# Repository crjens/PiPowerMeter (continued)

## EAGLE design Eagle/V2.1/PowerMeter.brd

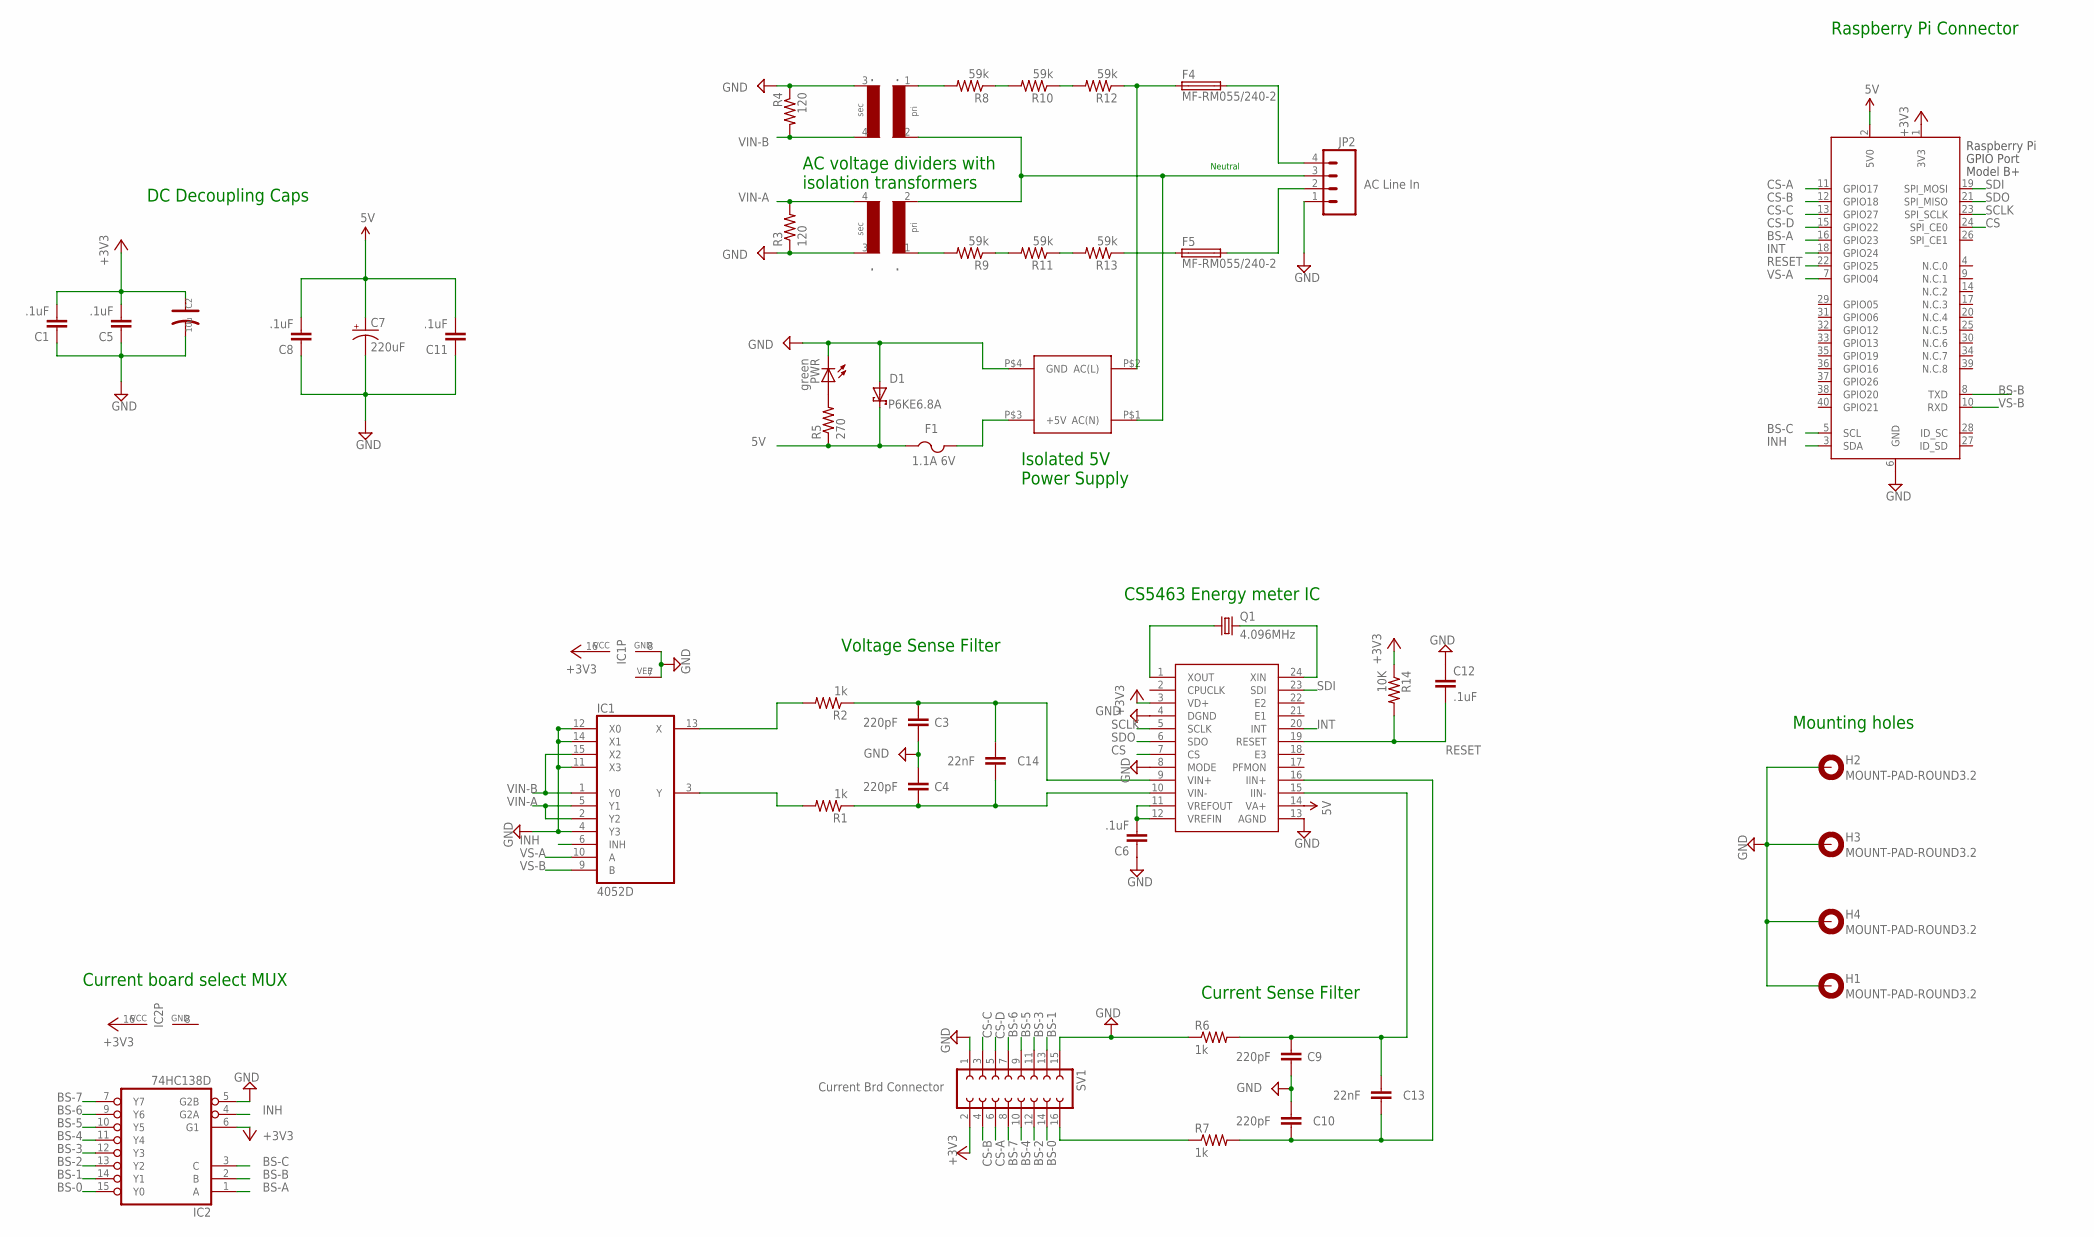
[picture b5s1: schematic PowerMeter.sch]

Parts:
C1, C5, C6, C8, C11, C12: .1uF; C1206; PARTNO C1206C104K5RAC7867
C2: 10u; AVX-C; PARTNO T491C106K016AT
C3, C4, C9, C10: 220pF; C1206; PARTNO C1206C221J5GACTU
C7: 220uF; E2,5-6E; PARTNO ESH227M016AE3AA
C13, C14: 22nF; C1206; PARTNO C1206C223K5RACTU
D1: P6KE6.8A; C1702-15; PARTNO P6KE6.8A
F1: 1.1A 6V; 1812; PARTNO 0ZCC0110AF2C
F4, F5: MF-RM055/240-2; TE5; PARTNO MF-RM055/240-2
H1, H2, H3, H4: MOUNT-PAD-ROUND3.2; 3,2-PAD
IC1: 4052D; SO16; PARTNO CD4052BNSR
IC2: 74HC138D; SO16; PARTNO SN74HC138NSR
JP2: AC Line In; SCREWTERMINAL-5MM-4; PARTNO 1935187
PWR: green; LED_1206; PARTNO LTST-C150GKT
Q1: 4.096MHz; HC49/S; PARTNO 9B-4.096MBBK-B
R1, R2, R6, R7: 1k; R1206; PARTNO RC1206FR-071KL
R3, R4: 120; R1206; PARTNO RC1206FR-07120RL
R5: 270; R1206; PARTNO RC1206FR-07270RL
R8, R9, R10, R11, R12, R13: 59k; R1206; PARTNO RC1206FR-0759KL
R14: 10K; R1206; PARTNO RC1206FR-0710KL
SV1: Current Brd Connector; FE08-2; PARTNO PPTC082LFBN-RC
U$2, U$3: TV16E
U$4: VSK-S10; PARTNO VSK-S5-5UA
U$5: CS5463; SSOP24; PARTNO CS5463-ISZ
X2: RASPI_BOARD_B+_E4; RASPI_BOARD_B+_EDGES_4DRILL; PARTNO M20-9762046

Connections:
5V: C7.+, C8.2, C11.2, D1.C, F1.1, R5.1, U$5.14 (VA+), X2.2 (5V0)
+3V3: C1.2, C2.+, C5.2, IC1.16 (VCC), IC2.6 (G1), IC2.16 (VCC), R14.1, SV1.2, U$5.3 (VD+), X2.1 (3V3)
+5V: F1.2, U$4.P$3 (+5V)
AC1: R8.2, U$3.1
AC(L): F4.1, R12.1, U$4.P$2 (AC(L))
AC(N): JP2.3, U$2.2, U$3.2, U$4.P$1 (AC(N))
BS-0: IC2.15 (Y0), SV1.14
BS-1: IC2.14 (Y1), SV1.13
BS-2: IC2.13 (Y2), SV1.12
BS-3: IC2.12 (Y3), SV1.11
BS-4: IC2.11 (Y4), SV1.10
BS-5: IC2.10 (Y5), SV1.9
BS-6: IC2.9 (Y6), SV1.7
BS-7: IC2.7 (Y7), SV1.8
BS-A: IC2.1 (A), X2.16 (GPIO23)
BS-B: IC2.2 (B), X2.8 (TXD)
BS-C: IC2.3 (C), X2.5 (SCL)
C5: C10.1, C13.1, R7.2, U$5.16 (IIN+)
CS: U$5.7 (CS), X2.24 (SPI_CE0)
CS-A: SV1.6, X2.11 (GPIO17)
CS-B: SV1.4, X2.12 (GPIO18)
CS-C: SV1.3, X2.13 (GPIO27)
CS-D: SV1.5, X2.15 (GPIO22)
GND: C1.1, C2.-, C3.1, C4.2, C5.1, C6.1, C7.-, C8.1, C9.1, C10.2, C11.1, C12.1, D1.A, H1.B3,2, H2.B3,2, H3.B3,2, H4.B3,2, IC1.4 (Y3), IC1.7 (VEE), IC1.8 (GND), IC1.11 (X3), IC1.12 (X0), IC1.14 (X1), IC2.5 (G2B), IC2.8 (GND), JP2.1, PWR.C, R3.1, R4.1, R6.1, SV1.1, SV1.15, U$2.3, U$3.3, U$4.P$4 (GND), U$5.4 (DGND), U$5.8 (MODE), U$5.13 (AGND), X2.6 (GND)
IIN+: R7.1, SV1.16
INH: IC1.6 (INH), IC2.4 (G2A), X2.3 (SDA)
INT: U$5.20 (INT), X2.18 (GPIO24)
unnamed: Q1.1, U$5.1 (XOUT)
unnamed: F5.1, R13.1
unnamed: PWR.A, R5.2
unnamed: C9.2, C13.2, R6.2, U$5.15 (IIN-)
unnamed: F4.2, JP2.4
unnamed: Q1.2, U$5.24 (XIN)
unnamed: C6.2, U$5.11 (VREFOUT), U$5.12 (VREFIN)
unnamed: IC1.13 (X), R2.2
unnamed: F5.2, JP2.2
unnamed: IC1.3 (Y), R1.2
unnamed: R10.1, R12.2
unnamed: R8.1, R10.2
unnamed: C4.1, C14.1, R1.1, U$5.10 (VIN-)
unnamed: R11.1, R13.2
unnamed: R9.1, R11.2
unnamed: R9.2, U$2.1
R1: C3.2, C14.2, R2.1, U$5.9 (VIN+)
RESET: C12.2, R14.2, U$5.19 (RESET), X2.22 (GPIO25)
SCLK: U$5.5 (SCLK), X2.23 (SPI_SCLK)
SDI: U$5.23 (SDI), X2.19 (SPI_MOSI)
SDO: U$5.6 (SDO), X2.21 (SPI_MISO)
VIN-A: IC1.2 (Y2), IC1.5 (Y1), R3.2, U$2.4
VIN-B: IC1.1 (Y0), IC1.15 (X2), R4.2, U$3.4
VS-A: IC1.10 (A), X2.7 (GPIO04)
VS-B: IC1.9 (B), X2.10 (RXD)

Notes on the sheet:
AC voltage dividers with isolation transformers
Isolated 5V Power Supply
Neutral
DC Decoupling Caps
Raspberry Pi Connector
CS5463 Energy meter IC
Voltage Sense Filter
Current Sense Filter
Current board select MUX
Mounting holes

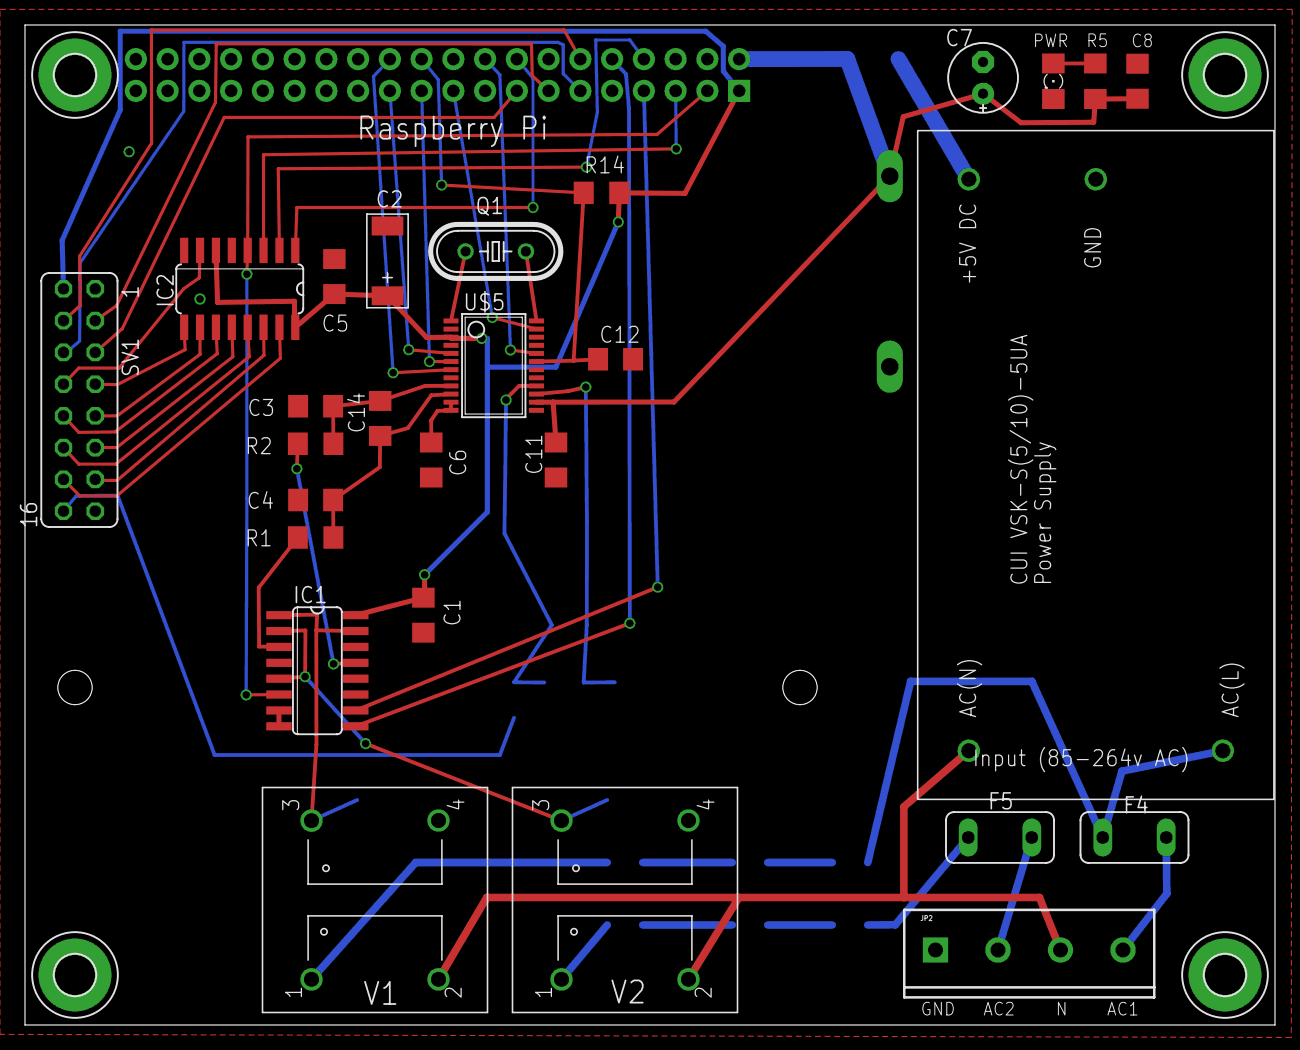
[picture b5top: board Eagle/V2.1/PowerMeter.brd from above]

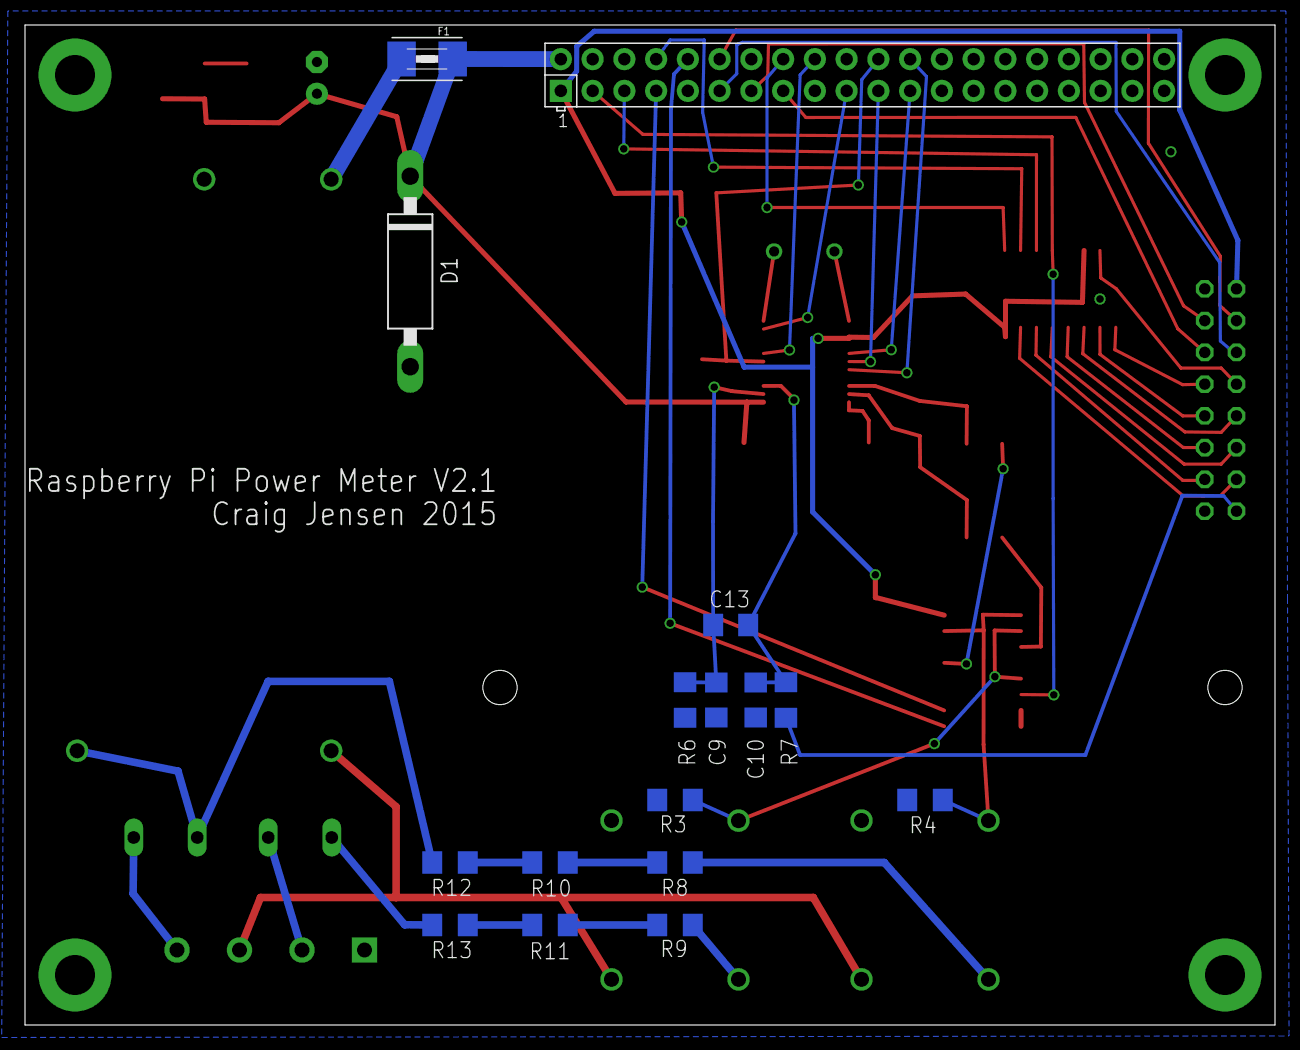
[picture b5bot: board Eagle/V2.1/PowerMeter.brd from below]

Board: 2 copper layers, 100.0 x 80.0 mm, 47 parts (16 on the bottom side), 52 nets.

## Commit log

2015-02-10 first
2015-02-10 update package file
2015-02-10 updated install files
2015-02-10 rename readme
2015-02-11 update version
2015-02-11 change update code to support git
2015-02-11 version summary
2015-02-11 include preinstall in package file
2015-02-11 updated logging
2015-02-11 updated version detection
2015-02-11 cleanup
2015-02-11 updated logic
2015-02-11 test
2015-02-11 iso date format
2015-02-11 fixed graph
2015-02-11 formatting update
2015-02-17 removed sudo when from npm install in app dir
2015-02-18 plot all probes on waveform graph
2015-02-18 revert back to node v0.10.28
2015-02-18 Add probe details for realtime view
2015-02-20 create process for reading from hardware
2015-02-27 remove old version
2015-03-05 removed total from circuits when only 1 probe
2015-03-20 add ability to set groupby in circuit view
2015-03-26 Added alerts
2015-03-26 add restart
2015-03-26 fix bar graph render
2015-03-31 fix hour graph
2015-05-04 Add Eagle files
2015-05-04 Fixed top and bottom images
2015-05-04 UX screenshots
2015-05-04 readme
2015-05-04 update screenshot
2015-05-07 Added system uptime
2015-05-07 remove mode and config and add Uptime to config
2015-05-07 fixed uptime
2015-05-07 make uptime readonly
2015-05-08 Add hardware photo
2015-05-29 added restore config
2015-05-29 clean up config
2015-06-01 Added config backup/restore
2015-06-01 Configuration backup and restore
2015-06-01 Updated Eagle files
2015-06-03 Fixed BOM for current board
2015-06-10 Added V2.2 Eagle files and removed old versions due to hardware bug
2015-06-17 Support of three voltage channels
2015-06-24 Improve perf of config update and fix crash when deleting circuits
2015-06-24 bug fix
2015-06-25 Remove legacy code for older hardware versions
2015-06-29 Update scale factors for V2.2 hardware
2015-06-30 add multer to package
2015-07-02 backup/restore configuration from file instead of text
2015-07-07 Added ability to set http port of web server
2015-07-07 Clean up shutdown code paths
2015-07-07 Add calculated line frequency
2015-07-07 Updated frequency calculation
2015-07-07 Fixed crash when adding new circuit
2015-07-08 Auto set fundamental frequency
2015-07-08 Improve frequency calculation
2015-07-09 Save calculated frequency to database
2015-07-09 Basic analytics
2015-07-10 Add universal-analytics to package
2015-07-10 update install script
2015-07-10 Updated install script
2015-07-10 gracefully handle missing analytics
2015-07-10 Clean up shutdown
2015-07-10 make sure reader process terminates when server is shut down
2015-07-24 Update zero crossing detection and add to result data
2015-07-24 Add zero crossing to plot
2015-07-24 disable zc in plot
2015-09-08 round cumulative results
2015-09-08 new state api
2015-09-09 fixed case on ReadState
2015-09-09 fix closure bug
2015-09-09 more closure bugs
2015-09-09 fix return
2015-09-25 MQTT support
2015-09-26 Fix Mqtt
2015-10-13 overload toFixed to fix rounding
2015-10-13 Replace toFixed with new round function
2015-11-07 Update default voltage scale factor
2015-11-08 allow negavite values
2015-11-10 locale support
2015-11-10 fix formatting
2015-11-12 return raw numbers
2015-11-12 update realtime
2015-11-12 fix display
2015-11-12 use globalize
2015-11-12 Switch over to jquery globalization
2015-11-13 updated formatting
2015-11-13 filter out default
2015-11-13 reduce rounding
2015-11-13 round db values
2015-11-17 update phase compensation
2015-12-10 update scale factors for current probes
2015-12-15 call reset every time
2015-12-15 update logging
2015-12-15 remove extraneous logging
2015-12-15 update package reference to cs5463
2015-12-15 check status and reset if needed
2015-12-16 Updated status checking
2015-12-16 status check
2015-12-16 logging update
2015-12-18 change scale factor for 30A probe
2015-12-19 add logging during reset
2015-12-19 additional null checks
2015-12-30 updated install instructions
2015-12-30 update install docs
2015-12-30 latest cs5463
2015-12-31 fix path to forever
2016-01-01 updated cs5463
2016-01-01 catch and handle errors in cs5463
2016-01-03 log sample time
2016-01-11 Update graph axes
2016-01-25 additional error handling
2016-04-11 updated cs5463 url
2016-05-04 Fix bug when offset is +
2016-05-08 Don't monitor LSD bit
2016-06-08 Update to latest Raspbian
2016-06-08 update link to lite version of Raspbian
2016-09-06 Add probe type
    0 = load only, 1 = source only, 2 = both
2016-09-06 Update sourcetype
2016-09-07 fix probe insert query
2016-09-07 Default SourceType to both
2016-09-07 fix sourcetype
2016-09-07 fix possible null ref
2016-09-19 zero current for sourcetypes 1 and 2
2017-04-10 add images
2017-04-10 update image
2017-09-09 Update readme and add breakers
2017-09-09 Fix readme
2017-09-09 updated breaker sizes
2017-12-14 Updated default sensors
2017-12-27 Added Test Support
2017-12-27 add advanced flag
2017-12-27 add missing files
2018-11-26 update install instructions
2019-01-06 refactor
2019-01-06 fix naming
2019-01-06 fix exports
2019-01-06 reorder
2019-01-06 fix frequency
2019-01-06 update cs5463
2019-01-06 fix data
2019-01-07 add setup.sh
2019-01-07 install spi
2019-01-07 add spi and uart setup
2019-01-07 fix path
2019-01-07 add cs5490 package
2019-01-07 fix spi
2019-01-08 Add cs5490
2019-01-09 auto detect
2019-01-09 fix read
2019-01-09 fix init
2019-01-09 init
2019-01-09 fix cs5463
2019-01-09 reset
2019-01-09 out pin fix
2019-01-15 Update README.md (must use `pi` user)
2019-01-19 update cs5490 dependency
2019-01-19 working version of cs5490
2019-01-19 add gitignore
2019-01-19 comment logging
2019-01-19 change pin mode
2019-01-19 update to latest packages
2019-01-19 update setup
2019-01-20 update setup script
2019-01-20 pi 1
2019-01-20 update install
2019-01-20 fix convert
2019-01-20 update installer
2019-01-21 setup
2019-01-21 improve board detection
2019-01-24 readme update
2019-01-29 Support additional voltage channels
2019-02-03 update db schema
2019-04-11 enable large config
2019-08-22 Fix part number for 59k resistors
    The 59k resistors list the part number etc for 1k resistors.
2019-10-05 add v4.0 eagle files
2019-10-30 fix current scale
2019-10-30 fix twilio
2019-11-05 add test mode
2019-11-07 add cyclecount
2019-11-07 add samplecount
2019-11-07 remove samplecount
2019-11-07 SampleCount
2019-11-07 fix samplecount
2019-11-08 Add SampleTime
2019-11-08 fix config
2019-11-08 config page
2019-11-08 config
2019-11-08 update config
2019-11-08 fix stop
2019-11-08 fix update
2019-11-08 restart
2019-11-08 stop
2019-11-08 cs5463
2019-11-09 auto reset
2019-11-09 move registervalues
2019-11-09 naming
2019-11-09 remove round
2019-11-09 formatting
2019-11-09 fix compare
2019-11-09 reset function
2019-11-09 fix reset
2019-11-09 update zxum
2019-11-09 format zxnum
2019-11-09 fix write register
2019-11-09 harden sample time
2019-11-09 validate zxnum
2019-11-09 fix zxnum
2019-11-10 validate form
2019-11-10 revert to master
2019-11-12 fix main page device name
2019-11-13 flot 0.8.3
2019-11-14 add version to config page
2019-11-17 password only auth
2019-11-18 digest auth
2019-11-18 comment auth
2019-11-18 add crypto
2019-11-18 ignore username
2019-11-18 fix username
2019-11-18 bypass auth on local
2019-11-18 fix auth
2019-12-15 update time picker
2019-12-15 fix mqtt and update time picker
2019-12-15 disable rollup
2019-12-15 fix datepicker width
2019-12-18 fix initial draw
2020-03-11 support for MqttClient options
2020-04-23 Update raspbian version
2021-12-31 Suppress forever logging to /root/.forever
